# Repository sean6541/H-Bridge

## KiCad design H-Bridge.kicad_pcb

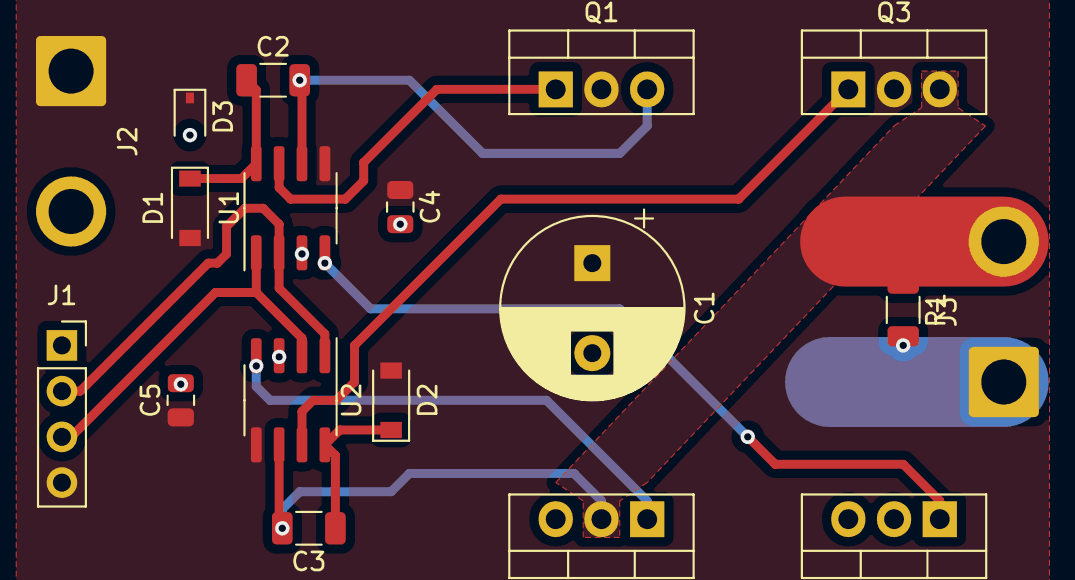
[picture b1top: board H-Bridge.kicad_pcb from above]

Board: 2 copper layers, 18 parts (0 on the bottom side), 12 nets.

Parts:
C1: 1000u; CP_Radial_D10.0mm_P5.00mm
C2, C3: 10u; C_1206_3216Metric
C4, C5: 0.1u; C_0805_2012Metric
D1, D2: D; D_SOD-123
D3: 18V; D_SOD-323
J1: Conn_01x04; PinSocket_1x04_P2.54mm_Vertical
J2, J3: Screw_Terminal_01x02; SolderWire-2sqmm_1x02_P7.8mm_D2mm_OD3.9mm
Q1, Q2, Q3, Q4: Q_NMOS_GDS; TO-220-3_Vertical
R1: 470; R_1206_3216Metric
U1, U2: IRS2181; SOIC-8_3.9x4.9mm_P1.27mm

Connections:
+12V: C1.1, C4.1, C5.1, D1.2, D2.2, D3.1, J1.4, J2.1, Q1.2, Q3.2, U1.5, U2.5
GND: C1.2, C4.2, C5.2, D3.2, J1.1, J2.2, Q2.3, Q4.3, U1.3, U2.3
unnamed: C2.1, D1.1, U1.8
unnamed: C3.1, D2.1, U2.8
unnamed: Q1.1, U1.7
unnamed: Q2.1, U1.4
unnamed: Q3.1, U2.7
unnamed: Q4.1, U2.4
OUT_A: C2.2, J3.1, Q1.3, Q2.2, R1.2, U1.6
OUT_B: C3.2, J3.2, Q3.3, Q4.2, R1.1, U2.6
SIG_A: J1.3, U1.1, U2.2
SIG_B: J1.2, U1.2, U2.1

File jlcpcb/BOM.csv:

Comment,Designator,Footprint,LCSC
"1000u","C1","Capacitor_THT:CP_Radial_D10.0mm_P5.00mm",""
"10u","C2,C3","Capacitor_SMD:C_1206_3216Metric","C13585"
"0.1u","C4,C5","Capacitor_SMD:C_0805_2012Metric","C49678"
"D","D1,D2","Diode_SMD:D_SOD-123","C64898"
"18V","D3","Diode_SMD:D_SOD-323","C124651"
"Conn_01x04","J1","Connector_PinSocket_2.54mm:PinSocket_1x04_P2.54mm_Vertical",""
"Screw_Terminal_01x02","J2,J3","Connector_Wire:SolderWire-2sqmm_1x02_P7.8mm_D2mm_OD3.9mm",""
"Q_NMOS_GDS","Q1,Q2,Q3,Q4","Package_TO_SOT_THT:TO-220-3_Vertical",""
"470","R1","Resistor_SMD:R_1206_3216Metric","C25383"
"IRS2181","U1,U2","Package_SO:SOIC-8_3.9x4.9mm_P1.27mm","C67284"

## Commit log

2020-06-03 Create PCB
2020-11-12 Add JLCPCB Files
